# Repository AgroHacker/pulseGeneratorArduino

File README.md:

# pulseGeneratorArduino
AD9954 based pulse generator -  Arduino Shield 

This project is currently in the early development process.  

A little background information.  This is my first major programming/maker/github project.  I am developing an open source soil moisture probe.  The pulse generator is just one component of this system.   More detail of the overall project will be added shortly.  

 Currently the eagle files will not correctly export gcode files with pcb gcode. Not sure why but the crash error reported by DrMingw is saved as ERROR-Dr.Mingw.txt

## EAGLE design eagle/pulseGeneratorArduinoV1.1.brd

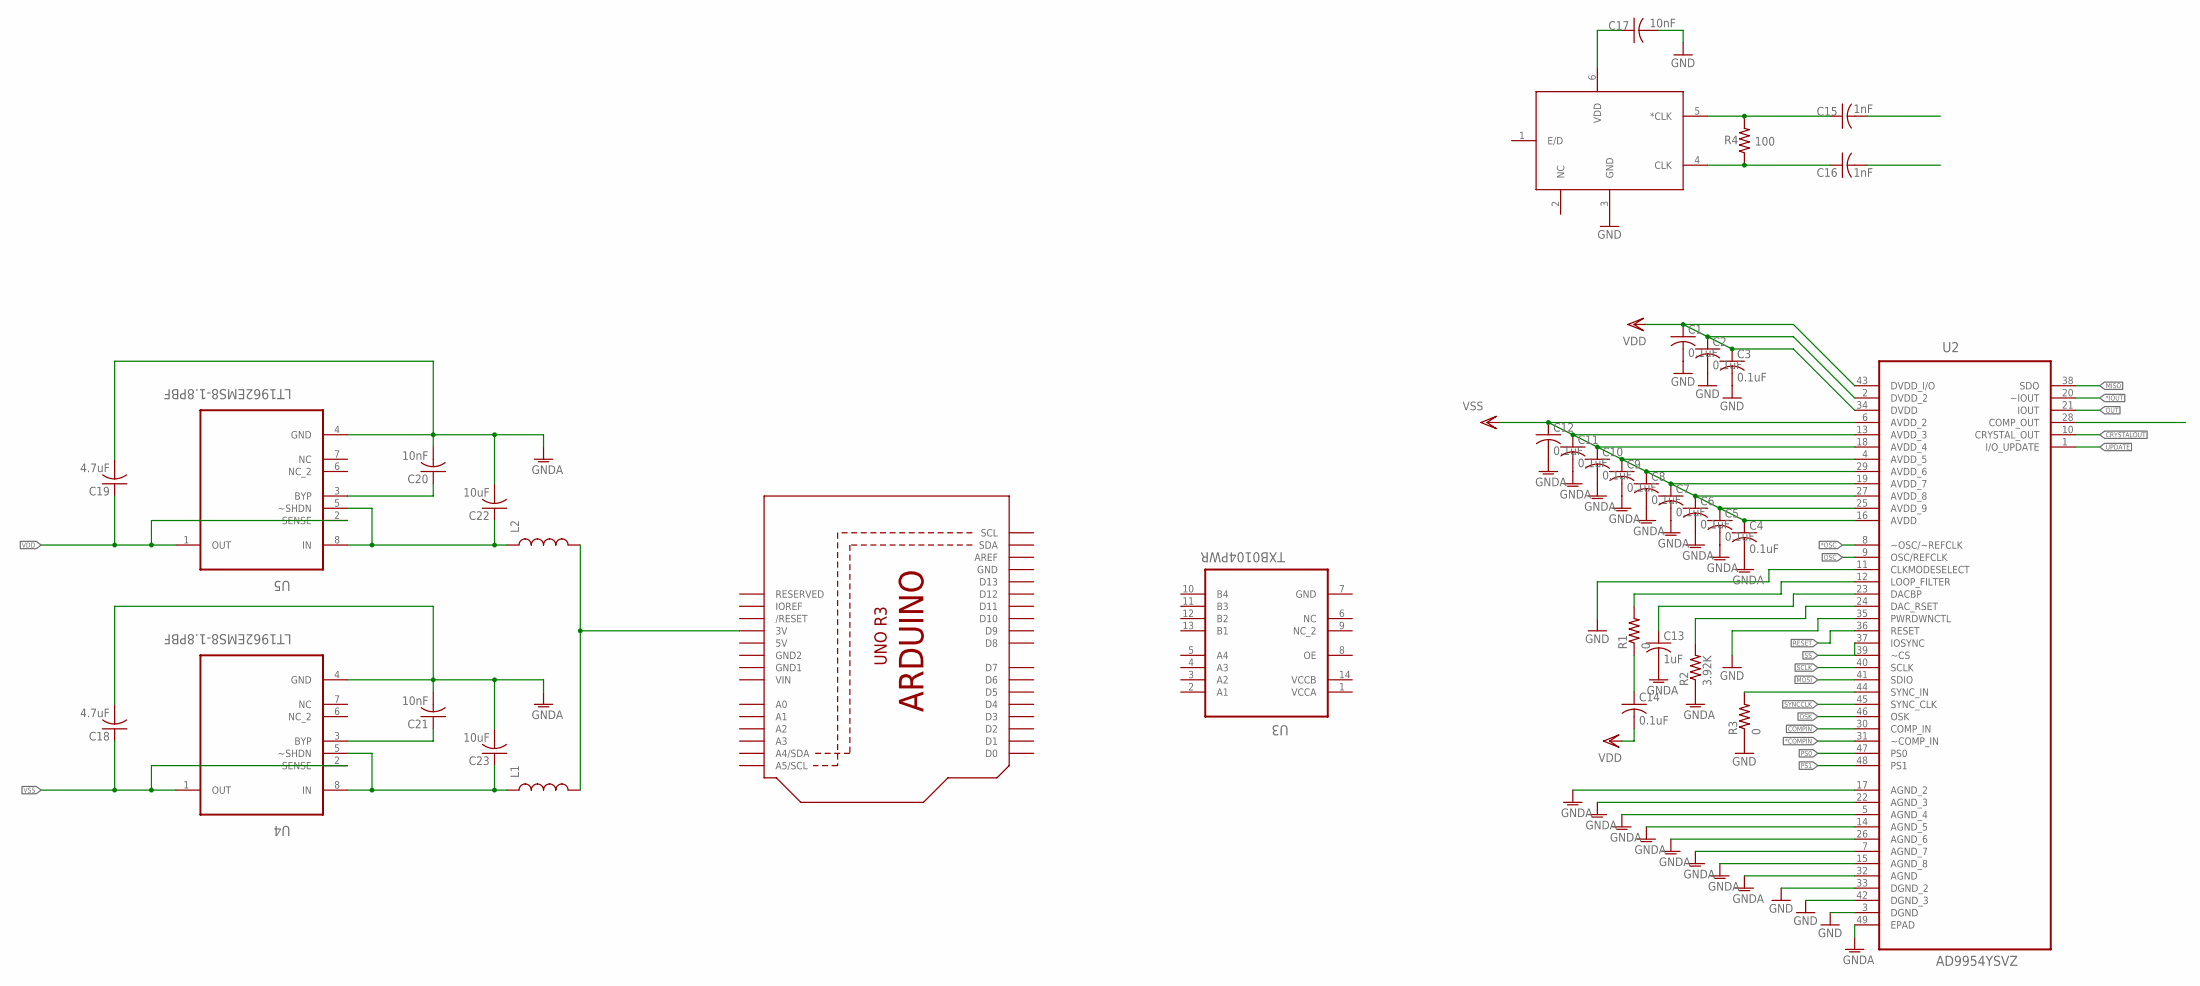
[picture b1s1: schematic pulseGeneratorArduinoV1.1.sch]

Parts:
C1, C2, C3, C4, C5, C6, C7, C8, C9, C10, C11, C12, C14: 0.1uF; C0402
C13: 1uF; C0402
C15, C16: 1nF; C0402
C17, C20, C21: 10nF; C0402
C18, C19: 4.7uF; C0402
C22, C23: 10uF; C0402
L1, L2: INDUCTOR0603; 0603
R1, R3: 0; R0402
R2: 3.92K; R0402
R4: 100; R0402
U1: ARDUINOR3-DIMENSION; ARDUINOR3
U2: AD9954YSVZ; QFP50P900X900X120-49N
U3: TXB0104PWR; SOP65P640X120-14N
U4, U5: LT1962EMS8-1.8PBF; SOP65P490X110-8N
U$1: FXO-LC53-100; 6-SMD-NOLEADS

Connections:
5V: U1.5V
*COMPIN: U2.31 (~COMP_IN)
*IOUT: U2.20 (~IOUT)
*OSC: C15.2, U2.8 (~OSC/~REFCLK)
COMPIN: U2.30 (COMP_IN)
CRYSTALOUT: U2.10 (CRYSTAL_OUT)
GND: C1.2, C2.2, C3.2, C17.2, R3.1, U1.GND, U2.3 (DGND), U2.11 (CLKMODESELECT), U2.33 (DGND_2), U2.35 (PWRDWNCTL), U2.42 (DGND_3), U$1.3 (GND)
GND1: U1.GND1
GND2: U1.GND2
GNDA: C4.2, C5.2, C6.2, C7.2, C8.2, C9.2, C10.2, C11.2, C12.2, C13.2, C18.2, C19.2, C20.2, C21.2, C22.2, C23.2, R2.1, U2.5 (AGND_4), U2.7 (AGND_7), U2.14 (AGND_5), U2.15 (AGND_8), U2.17 (AGND_2), U2.22 (AGND_3), U2.26 (AGND_6), U2.32 (AGND), U2.49 (EPAD), U4.4 (GND), U5.4 (GND)
MISO: U2.38 (SDO)
MOSI: U2.41 (SDIO)
unnamed: C14.1, R1.1
unnamed: C16.1, R4.1, U$1.4 (CLK)
unnamed: R3.2, U2.44 (SYNC_IN)
unnamed: C15.1, R4.2, U$1.5 (*CLK)
unnamed: R1.2, U2.12 (LOOP_FILTER)
unnamed: C13.1, U2.23 (DACBP)
unnamed: R2.2, U2.24 (DAC_RSET)
unnamed: C17.1, U$1.6 (VDD)
unnamed: C22.1, L2.1, U5.5 (~SHDN), U5.8 (IN)
unnamed: C23.1, L1.1, U4.5 (~SHDN), U4.8 (IN)
unnamed: C20.1, U5.3 (BYP)
unnamed: C21.1, U4.3 (BYP)
unnamed: L1.2, L2.2, U1.3V
OSC: C16.2, U2.9 (OSC/REFCLK)
OSK: U2.46 (OSK)
OUT: U2.21 (IOUT)
PS0: U2.47 (PS0)
PS1: U2.48 (PS1)
RESET: U2.36 (RESET)
SCLK: U2.40 (SCLK)
SS: U2.37 (IOSYNC), U2.39 (~CS)
SYNCCLK: U2.45 (SYNC_CLK)
UPDATE: U2.1 (I/O_UPDATE)
VCCA: U3.1 (VCCA)
VCCB: U3.14 (VCCB)
VDD: C1.1, C2.1, C3.1, C14.2, C19.1, U2.2 (DVDD_2), U2.34 (DVDD), U2.43 (DVDD_I/O), U5.1 (OUT), U5.2 (SENSE)
VIN: U1.VIN
VSS: C4.1, C5.1, C6.1, C7.1, C8.1, C9.1, C10.1, C11.1, C12.1, C18.1, U2.4 (AVDD_5), U2.6 (AVDD_2), U2.13 (AVDD_3), U2.16 (AVDD), U2.18 (AVDD_4), U2.19 (AVDD_7), U2.25 (AVDD_9), U2.27 (AVDD_8), U2.29 (AVDD_6), U4.1 (OUT), U4.2 (SENSE)

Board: 2 copper layers, 35 parts (0 on the bottom side), 20 nets, no tracks yet.

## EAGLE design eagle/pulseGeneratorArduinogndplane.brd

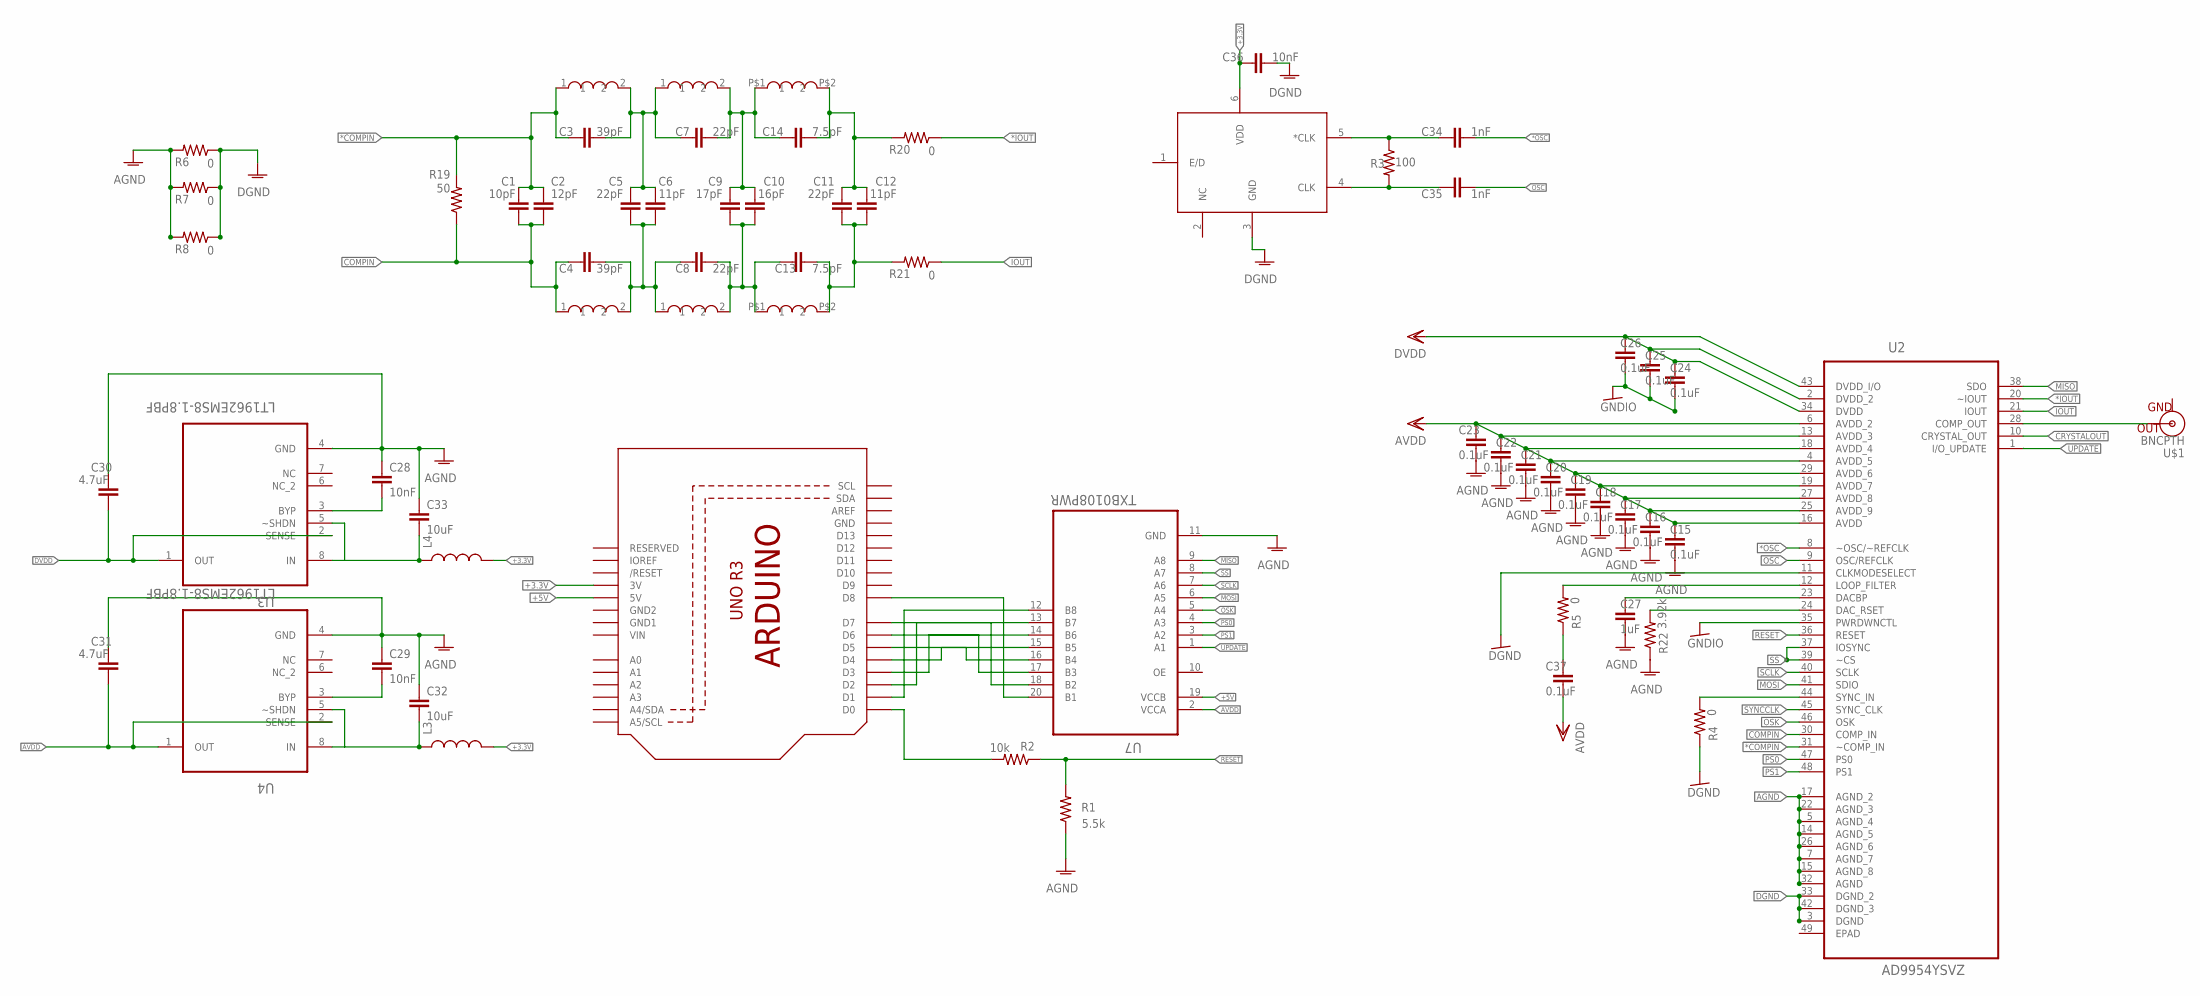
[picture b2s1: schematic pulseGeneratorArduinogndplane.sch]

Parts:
C1: 10pF; C0603K
C2: 12pF; C0603K
C3, C4: 39pF; C0603K
C5, C7, C8, C11: 22pF; C0603K
C6, C12: 11pF; C0603K
C9: 17pF; C0603K
C10: 16pF; C0603K
C13, C14: 7.5pF; C0603K
C15, C16, C17, C18, C19, C20, C21, C22, C23, C24, C25, C26, C37: 0.1uF; C1005
C27: 1uF; C1005
C28, C29, C36: 10nF; C0603K
C30, C31: 4.7uF; C0603K
C32, C33: 10uF; C0603K
C34, C35: 1nF; C0603K
L3, L4: INDUCTOR0603; 0603
R1: 5.5k; R0402
R2: 10k; R0402
R3: 100; R0402
R4, R5, R6, R7, R8, R20, R21: 0; R0402
R19: 50; R0402
R22: 3.92k; R0402
U1: ARDUINOR3-DIMENSION; ARDUINOR3
U2: AD9954YSVZ; QFP50P900X900X120-49N
U3, U4: LT1962EMS8-1.8PBF; SOP65P490X110-8N
U7: TXB0108PWR; SOP65P640X120-20N
U$1: BNCPTH; BNC
U$2: FXO-LC53-100; 6-SMD-NOLEADS
U$3, U$4, U$5, U$6: 1080HQ; 1080
U$7, U$8: 0805HQ; 0805

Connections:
*COMPIN: C1.1, C2.1, C3.1, R19.2, U2.31 (~COMP_IN), U$4.1
*IOUT: R20.1, U2.20 (~IOUT)
*OSC: C34.1, U2.8 (~OSC/~REFCLK)
+3.3V: C32.2, C33.2, C36.2, L3.1, L3.2, L4.1, L4.2, U1.3V, U3.5 (~SHDN), U3.8 (IN), U4.5 (~SHDN), U4.8 (IN), U$2.6 (VDD)
+5V: U1.5V, U7.19 (VCCB)
AGND: C15.2, C16.2, C17.2, C18.2, C19.2, C20.2, C21.2, C22.2, C23.2, C27.2, C28.1, C29.1, C30.1, C31.1, C32.1, C33.1, R1.1, R6.2, R7.2, R8.2, R22.1, U2.5 (AGND_4), U2.7 (AGND_7), U2.14 (AGND_5), U2.15 (AGND_8), U2.17 (AGND_2), U2.22 (AGND_3), U2.26 (AGND_6), U2.32 (AGND), U3.4 (GND), U4.4 (GND), U7.11 (GND)
AVDD: C15.1, C16.1, C17.1, C18.1, C19.1, C20.1, C21.1, C22.1, C23.1, C31.2, C37.2, U2.4 (AVDD_5), U2.6 (AVDD_2), U2.13 (AVDD_3), U2.16 (AVDD), U2.18 (AVDD_4), U2.19 (AVDD_7), U2.25 (AVDD_9), U2.27 (AVDD_8), U2.29 (AVDD_6), U4.1 (OUT), U4.2 (SENSE), U7.2 (VCCA)
COMPIN: C1.2, C2.2, C4.1, R19.1, U2.30 (COMP_IN), U$3.1
CRYSTALOUT: U2.10 (CRYSTAL_OUT)
DGND: C24.2, C25.2, C26.2, C36.1, R4.1, R6.1, R7.1, R8.1, U2.3 (DGND), U2.11 (CLKMODESELECT), U2.33 (DGND_2), U2.35 (PWRDWNCTL), U2.42 (DGND_3), U$2.3 (GND)
DVDD: C24.1, C25.1, C26.1, C30.2, U2.2 (DVDD_2), U2.34 (DVDD), U2.43 (DVDD_I/O), U3.1 (OUT), U3.2 (SENSE)
GND: U1.GND
GND1: U1.GND1
GND2: U1.GND2
IOUT: R21.1, U2.21 (IOUT)
MISO: U2.38 (SDO), U7.9 (A8)
MOSI: U2.41 (SDIO), U7.6 (A5)
unnamed: U2.28 (COMP_OUT), U$1.S (OUT)
unnamed: R22.2, U2.24 (DAC_RSET)
unnamed: U1.D8, U7.20 (B1)
unnamed: U1.D7, U7.18 (B2)
unnamed: U1.D6, U7.17 (B3)
unnamed: U1.D5, U7.16 (B4)
unnamed: U1.D1, U7.12 (B8)
unnamed: U1.D2, U7.13 (B7)
unnamed: U1.D3, U7.14 (B6)
unnamed: U1.D4, U7.15 (B5)
unnamed: R2.2, U1.D0
unnamed: C7.1, C9.2, C10.2, C14.2, U$5.2, U$7.P$1 (1)
unnamed: C8.1, C9.1, C10.1, C13.2, U$6.2, U$8.P$1 (1)
unnamed: C3.2, C5.2, C6.2, C7.2, U$4.2, U$5.1
unnamed: C27.1, U2.23 (DACBP)
unnamed: C4.2, C5.1, C6.1, C8.2, U$3.2, U$6.1
unnamed: C35.2, R3.2, U$2.4 (CLK)
unnamed: C29.2, U4.3 (BYP)
unnamed: C34.2, R3.1, U$2.5 (*CLK)
unnamed: C28.2, U3.3 (BYP)
unnamed: R4.2, U2.44 (SYNC_IN)
unnamed: R5.2, U2.12 (LOOP_FILTER)
unnamed: C37.1, R5.1
unnamed: C11.1, C12.1, C13.1, R21.2, U$8.P$2 (2)
unnamed: C11.2, C12.2, C14.1, R20.2, U$7.P$2 (2)
OSC: C35.1, U2.9 (OSC/REFCLK)
OSK: U2.46 (OSK), U7.5 (A4)
PS0: U2.47 (PS0), U7.4 (A3)
PS1: U2.48 (PS1), U7.3 (A2)
RESET: R1.2, R2.1, U2.36 (RESET)
SCLK: U2.40 (SCLK), U7.7 (A6)
SS: U2.37 (IOSYNC), U2.39 (~CS), U7.8 (A7)
SYNCCLK: U2.45 (SYNC_CLK)
UPDATE: U2.1 (I/O_UPDATE), U7.1 (A1)
VIN: U1.VIN

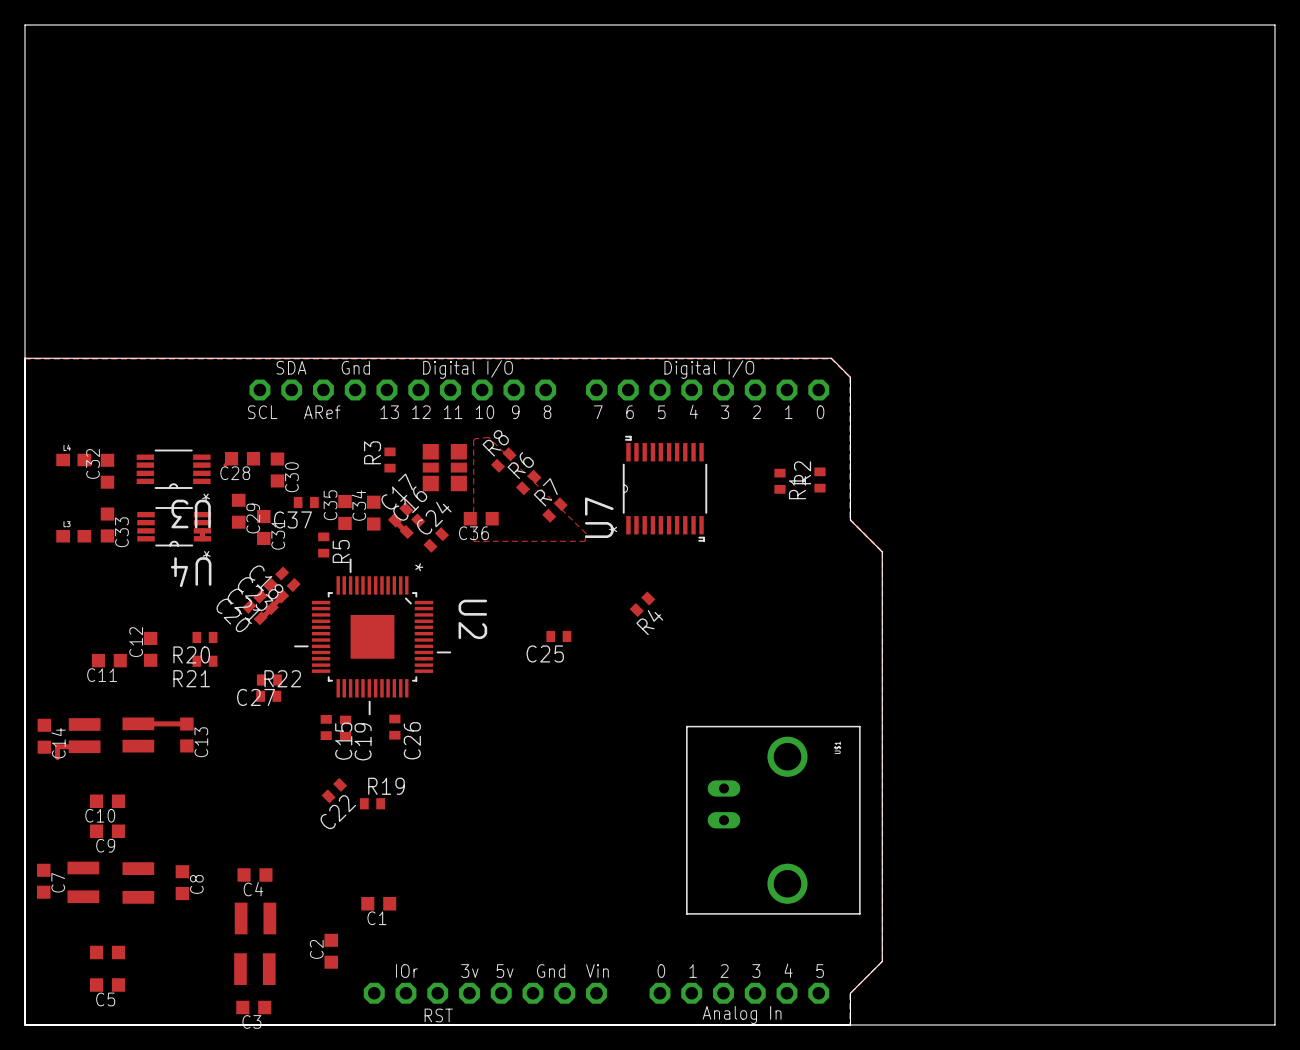
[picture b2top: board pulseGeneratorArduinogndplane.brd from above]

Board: 2 copper layers, 100.0 x 80.0 mm, 64 parts (0 on the bottom side), 46 nets.

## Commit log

2015-03-04 Deleted .gitignore file
    No sure what this file is for or how to use it properly.
2015-03-04 Added in eagle files
    Initial Commit of PCB files
2015-03-04 added eagle error file
    This file is produced from Dr.Mingw program when pcb-gcode is ran
2015-03-04 test
    Wanted to see how eagle and github worked together
2015-03-06 Deleted all routes to try and fix.
    This did not stop the crash
2015-03-06 Deleted board files
2015-03-06 Revert "Deleted board files"
    This reverts commit 1dcdb88fcdf8c4e404ee760a7f7773ee9e3a79e5.
2015-03-06 Revert "Deleted all routes to try and fix."
    This reverts commit 5f491c1068aea24b9851c2c5770cd8edc15ed6a6.
2015-03-06 Added V1.1 board
    Reverted file changes to pulsegeneratorgndshield
2015-03-06 made progress

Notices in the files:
parts and their libraries:
SparkFun-Passives: Licensing: Creative Commons ShareAlike 4.0 International - https://creativecommons.org/licenses/by-sa/4.0
